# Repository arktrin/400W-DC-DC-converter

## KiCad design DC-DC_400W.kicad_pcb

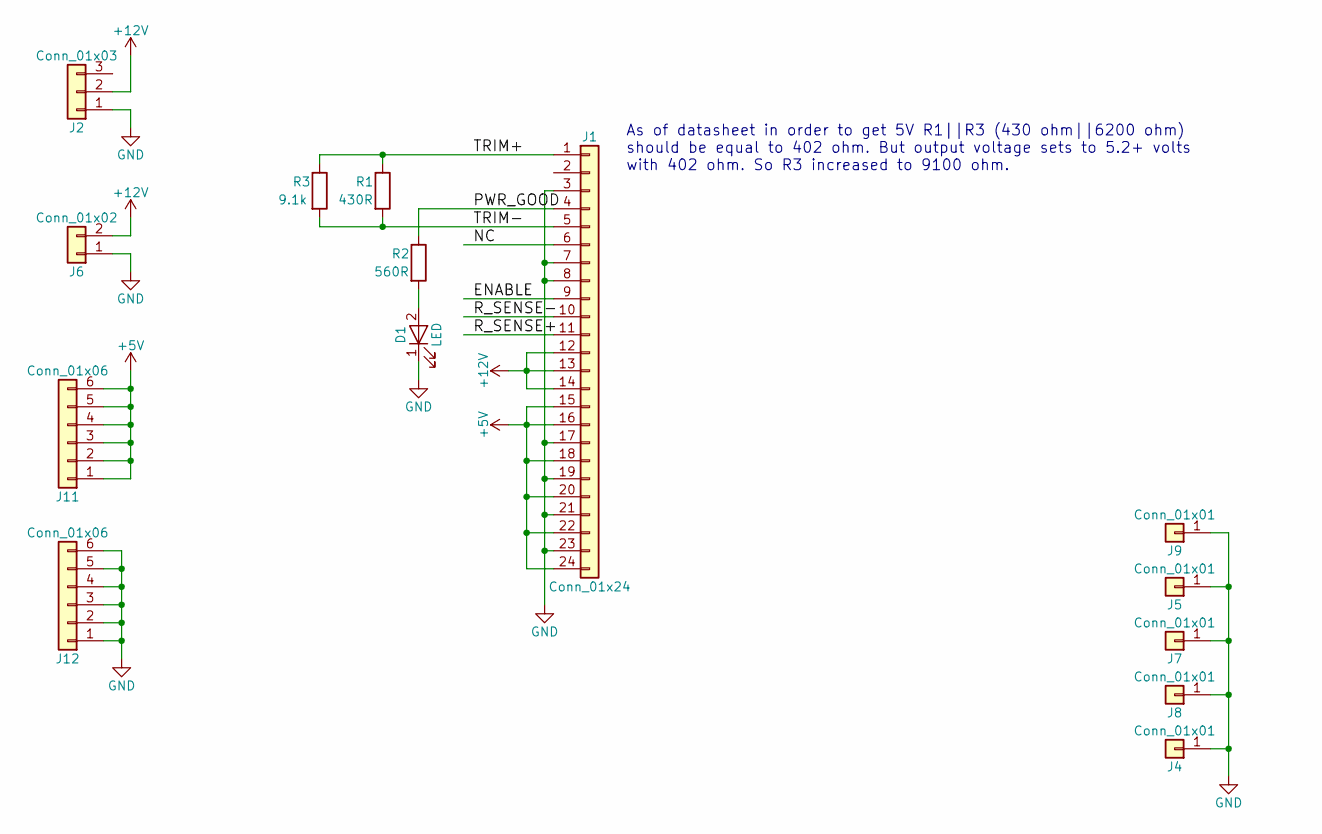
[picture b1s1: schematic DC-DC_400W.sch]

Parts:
D1: LED; D_0603
J1: Conn_01x24; Pin_Header_Straight_1x24_Pitch2.54mm
J2: Conn_01x03; Fan_Pin_Header_Straight_1x03
J4, J5, J7, J8, J9: Conn_01x01; MountingHole_3.2mm_M3_ISO7380_Pad
J6: Conn_01x02; XT60
J11, J12: Conn_01x06; PhoenixContact_MSTBVA-G_06x5.00mm_Vertical
R1: 430R; R_0603
R2: 560R; R_0603
R3: 9.1k; R_0603

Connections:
+5V: J1.15, J1.16, J1.18, J1.20, J1.22, J1.24, J11.1, J11.2, J11.3, J11.4, J11.5, J11.6
+12V: J1.12, J1.13, J1.14, J2.2, J6.2
/ENABLE: J1.9
/NC: J1.6
/PWR_GOOD: J1.4, R2.1
/R_SENSE+: J1.11
/R_SENSE-: J1.10
/TRIM+: J1.1, R1.1, R3.1
/TRIM-: J1.5, R1.2, R3.2
GND: D1.1 (K), J1.3, J1.7, J1.8, J1.17, J1.19, J1.21, J1.23, J2.1, J4.1, J5.1, J6.1, J7.1, J8.1, J9.1, J12.1, J12.2, J12.3, J12.4, J12.5, J12.6
unnamed: D1.2 (A), R2.2

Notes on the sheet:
As of datasheet in order to get 5V R1||R3 (430 ohm||6200 ohm) should be equal to 402 ohm. But output voltage sets to 5.2+ volts with 402 ohm. So R3 increased to 9100 ohm.

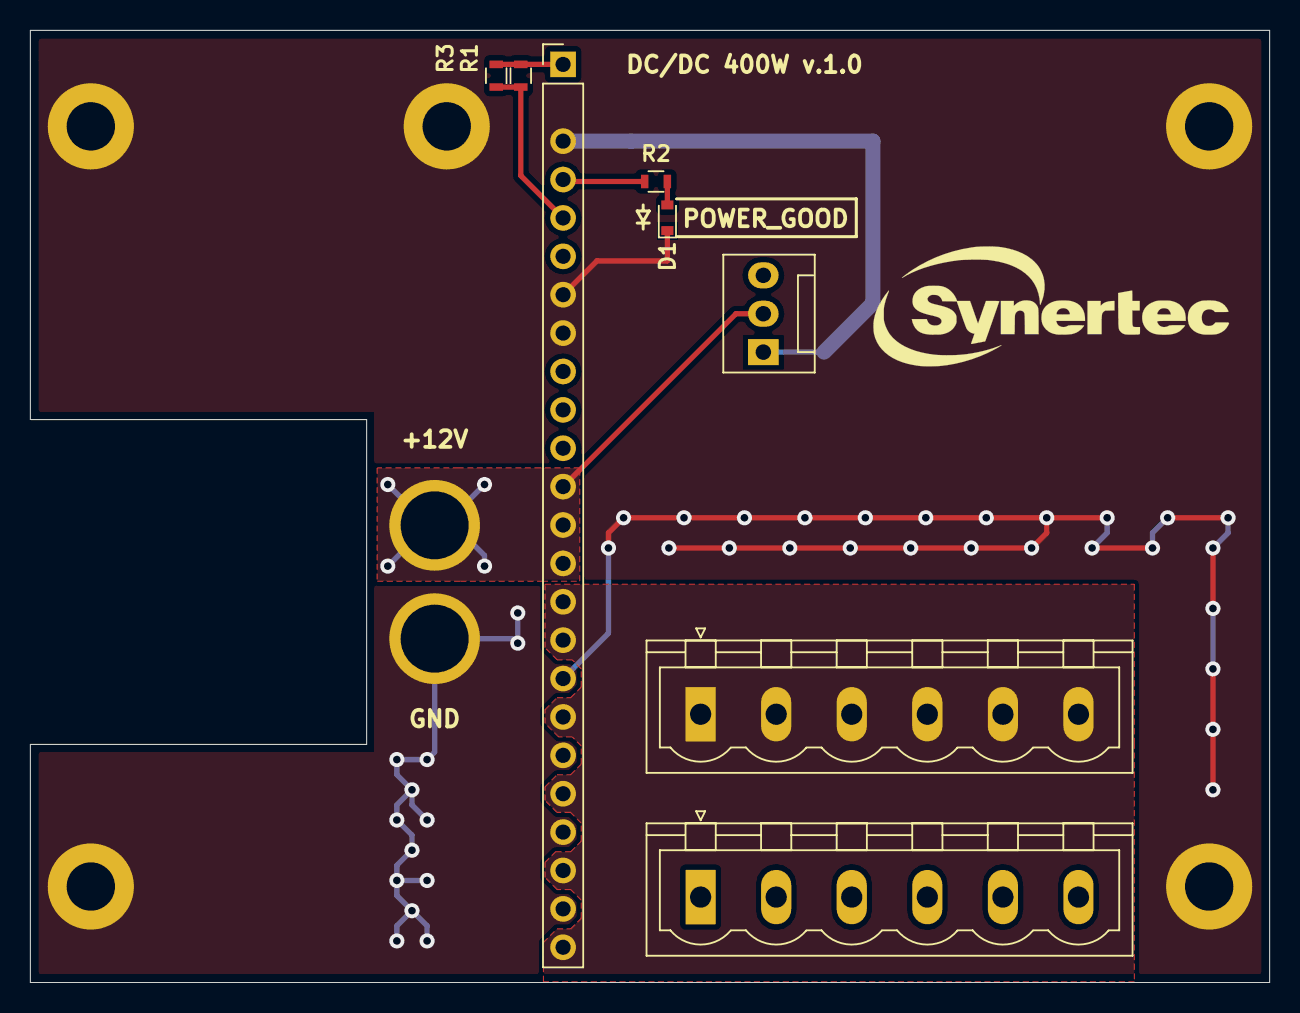
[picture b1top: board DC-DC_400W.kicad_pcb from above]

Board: 2 copper layers, 82.0 x 63.0 mm, 14 parts (1 on the bottom side), 7 nets.

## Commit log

2018-01-05 fancy power planes
2018-01-05 move to XT60 connector
2018-01-08 only one XT60 at the input
2018-01-11 remove unused XT60 connector, shrink pcb
2018-01-12 some progress on pcb
2018-01-13 gerber generated + pcb fixes
2018-01-15 almost done
2018-01-15 new gerber.zip
2018-01-16 final test version
2018-02-11 final 1.0 version
2018-02-16 0.35mm/0.35mm
2018-03-06 correct R1 and R3 in schematic
2018-03-06 correct symbol place in schematic
2018-03-28 silkscreen fix
